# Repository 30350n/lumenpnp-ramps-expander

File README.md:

## LumenPnP Ramps Expander

**Warning: This design hasn't been ordered/tested yet. Use at your own risk.**

I created this board to use as an expander for the MKS Gen L v2.1 I use to as a motherboard for
my LumenPnP.

It offers:

- 2 additional stepper drivers
- RS485 driver for feeders
- analog REV03 style vacuum sensors (I2C ADC option)
- extra power input to power feeders from a different (12V) PSU

While this was originally designed for the MKS Gen L v2.1, it should generally be compatible
with all ATmega2560 based RAMPS boards and maybe even other 3d printer boards that have the
12864 display expansion connectors.

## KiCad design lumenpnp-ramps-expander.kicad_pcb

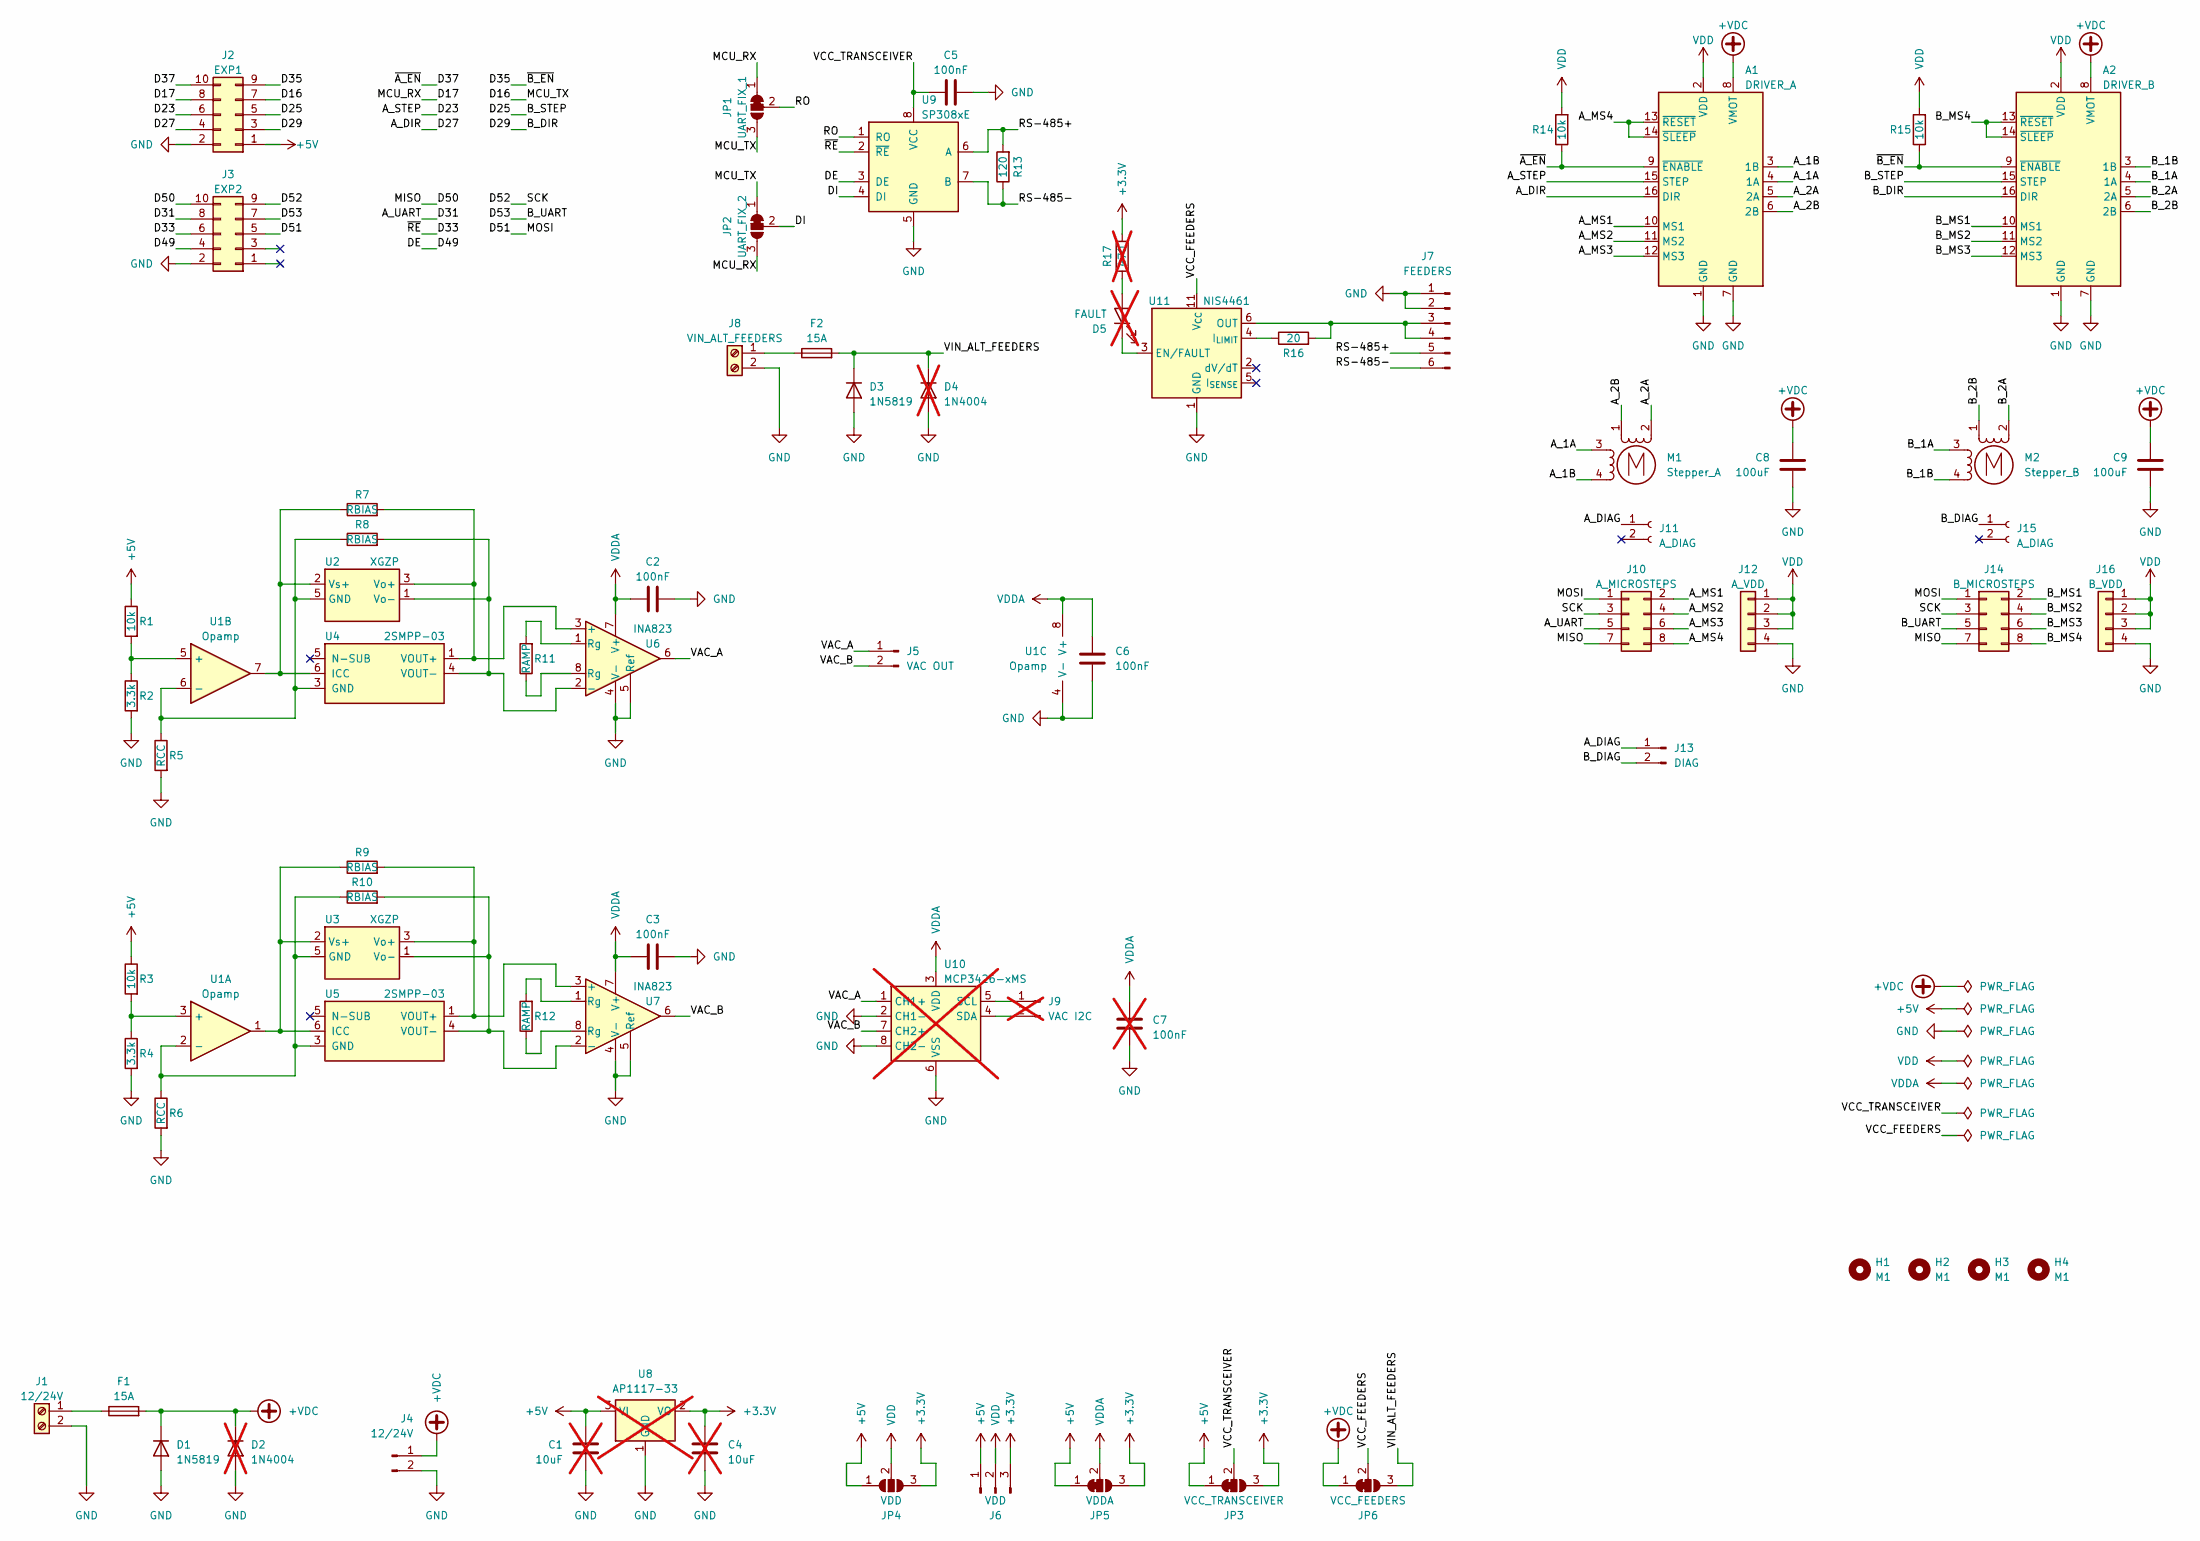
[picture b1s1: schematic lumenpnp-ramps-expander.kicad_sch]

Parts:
A1: DRIVER_A; Pololu_Breakout-16_15.2x20.3mm
A2: DRIVER_B; Pololu_Breakout-16_15.2x20.3mm
C1, C4: 10uF; C_1206_3216Metric; not fitted
C2, C3, C5, C6: 100nF; C_0603_1608Metric
C7: 100nF; C_0603_1608Metric; not fitted
C8, C9: 100uF; CP_Elec_6.3x7.7
D1, D3: 1N5819; D_SOD-123
D2, D4: 1N4004; D_DO-41_SOD81_P7.62mm_Horizontal; not fitted
D5: FAULT; LED_0603_1608Metric; not fitted
F1, F2: 15A; Fuse_1206_3216Metric
H1, H2, H3, H4: M1; MountingHole_3.2mm_M3_Pad
J1: 12/24V; TerminalBlock_Phoenix_MKDS-1,5-2-5.08_1x02_P5.08mm_Horizont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
J2: EXP1; IDC-Header_2x05_P2.54mm_Vertical
J3: EXP2; IDC-Header_2x05_P2.54mm_Vertical
J4: 12/24V; JST_XH_B2B-XH-A_1x02_P2.50mm_Vertical
J5: VAC OUT; JST_XH_B2B-XH-A_1x02_P2.50mm_Vertical
J6: VDD; PinHeader_1x03_P2.54mm_Vertical
J7: FEEDERS; IDC-Header_2x03_P2.54mm_Vertical
J8: VIN_ALT_FEEDERS; TerminalBlock_Phoenix_MKDS-1,5-2-5.08_1x02_P5.08mm_Horizont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
J9: VAC I2C; JST_XH_B2B-XH-A_1x02_P2.50mm_Vertical; not fitted
J10: A_MICROSTEPS; PinHeader_2x04_P2.54mm_Vertical
J11, J15: A_DIAG; PinSocket_1x02_P2.54mm_Vertical
J12: A_VDD; PinHeader_1x04_P2.54mm_Vertical
J13: DIAG; JST_XH_B2B-XH-A_1x02_P2.50mm_Vertical
J14: B_MICROSTEPS; PinHeader_2x04_P2.54mm_Vertical
J16: B_VDD; PinHeader_1x04_P2.54mm_Vertical
JP1: UART_FIX_1; SolderJumper-3_P1.3mm_Bridged12_RoundedPad1.0x1.5mm
JP2: UART_FIX_2; SolderJumper-3_P1.3mm_Bridged12_RoundedPad1.0x1.5mm
JP3: VCC_TRANSCEIVER; SolderJumper-3_P1.3mm_Bridged12_RoundedPad1.0x1.5mm
JP4: VDD; SolderJumper-3_P1.3mm_Open_RoundedPad1.0x1.5mm_NumberLabels
JP5: VDDA; SolderJumper-3_P1.3mm_Bridged12_RoundedPad1.0x1.5mm
JP6: VCC_FEEDERS; SolderJumper-3_P1.3mm_Bridged12_RoundedPad1.0x1.5mm
M1: Stepper_A; JST_XH_B4B-XH-A_1x04_P2.50mm_Vertical
M2: Stepper_B; JST_XH_B4B-XH-A_1x04_P2.50mm_Vertical
R1, R3, R14, R15: 10k; R_0603_1608Metric
R2, R4: 3.3k; R_0603_1608Metric
R5, R6: RCC; R_0603_1608Metric
R7, R8, R9, R10: RBIAS; R_0603_1608Metric
R11, R12: RAMP; R_0603_1608Metric
R13: 120; R_0603_1608Metric
R16: 20; R_0603_1608Metric
R17: 470; R_0603_1608Metric; not fitted
U1: Opamp; SOIC-8_3.9x4.9mm_P1.27mm
U2, U3: XGZP; SO-6_7x7mm_P2.54mm
U4, U5: 2SMPP-03
U6, U7: INA823; SOIC-8_3.9x4.9mm_P1.27mm
U8: AP1117-33; SOT-223-3_TabPin2; not fitted
U9: SP308xE; SOIC-8_3.9x4.9mm_P1.27mm
U10: MCP3426-xMS; SOIC-8_3.9x4.9mm_P1.27mm; not fitted
U11: NIS4461; WDFN-10-1EP_3x3mm_P0.5mm_EP1.8x2.5mm

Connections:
+3.3V: C4.1, J6.3, JP3.3 (B), JP4.3 (B), JP5.3 (B), R17.2, U8.2 (VO)
+5V: C1.1, J2.1, J6.1, JP3.1 (A), JP4.1 (A), JP5.1 (A), R1.1, R3.1, U8.3 (VI)
+VDC: A1.8 (VMOT), A2.8 (VMOT), C8.1, C9.1, D1.1 (K), D2.1 (K), F1.2, J4.1, JP6.1 (A)
/A_1A: A1.4 (1A), M1.3
/A_1B: A1.3 (1B), M1.4
/A_2A: A1.5 (2A), M1.2 (-)
/A_2B: A1.6 (2B), M1.1
/A_DIAG: J11.1, J13.1
/A_DIR: A1.16 (DIR), J2.4
/A_MS1: A1.10 (MS1), J10.2
/A_MS2: A1.11 (MS2), J10.4
/A_MS3: A1.12 (MS3), J10.6
/A_MS4: A1.13 (~RESET), A1.14 (~SLEEP), J10.8
/A_STEP: A1.15 (STEP), J2.6
/A_UART: J3.8, J10.5
/B_1A: A2.4 (1A), M2.3
/B_1B: A2.3 (1B), M2.4
/B_2A: A2.5 (2A), M2.2 (-)
/B_2B: A2.6 (2B), M2.1
/B_DIAG: J13.2, J15.1
/B_DIR: A2.16 (DIR), J2.3
/B_MS1: A2.10 (MS1), J14.2
/B_MS2: A2.11 (MS2), J14.4
/B_MS3: A2.12 (MS3), J14.6
/B_MS4: A2.13 (~RESET), A2.14 (~SLEEP), J14.8
/B_STEP: A2.15 (STEP), J2.5
/B_UART: J3.7, J14.5
/D16: J2.7, JP1.3 (B), JP2.1 (A)
/D17: J2.8, JP1.1 (A), JP2.3 (B)
/D33: J3.6, U9.2 (~RE)
/D35: A2.9 (~ENABLE), J2.9, R15.1
/D37: A1.9 (~ENABLE), J2.10, R14.1
/D49: J3.4, U9.3 (DE)
/D50: J3.10, J10.7, J14.7
/D51: J3.5, J10.1, J14.1
/D52: J3.9, J10.3, J14.3
/DI: JP2.2 (C), U9.4 (DI)
/RO: JP1.2 (C), U9.1 (RO)
/RS-485+: J7.5, R13.2, U9.6 (A)
/RS-485-: J7.6, R13.1, U9.7 (B)
/VAC_A: J5.1, U6.6, U10.1 (CH1+)
/VAC_B: J5.2, U7.6, U10.7 (CH2+)
/VCC_FEEDERS: JP6.2 (C), U11.11 (V_{CC})
/VCC_TRANSCEIVER: C5.1, JP3.2 (C), U9.8 (VCC)
/VIN_ALT_FEEDERS: D3.1 (K), D4.1 (K), F2.2, JP6.3 (B)
GND: A1.1 (GND), A1.7 (GND), A2.1 (GND), A2.7 (GND), C1.2, C2.2, C3.2, C4.2, C5.2, C6.2, C7.2, C8.2, C9.2, D1.2 (A), D2.2 (A), D3.2 (A), D4.2 (A), J1.2, J2.2, J3.2, J4.2, J7.1, J7.2, J8.2, J12.4, J16.4, R2.2, R4.2, R5.2, R6.2, U1.4 (V-), U6.4 (V-), U6.5 (Ref), U7.4 (V-), U7.5 (Ref), U8.1 (GND), U9.5 (GND), U10.2 (CH1-), U10.6 (VSS), U10.8 (CH2-), U11.1 (GND)
unnamed: D5.2 (A), R17.1
unnamed: D5.1 (K), U11.3 (EN/FAULT)
unnamed: F1.1, J1.1
unnamed: J7.3, J7.4, R16.2, U11.6 (OUT), U11.7 (OUT), U11.8 (OUT), U11.9 (OUT), U11.10 (OUT)
unnamed: F2.1, J8.1
unnamed: J9.1, U10.5 (SCL)
unnamed: J9.2, U10.4 (SDA)
unnamed: R11.1, U6.8 (Rg)
unnamed: R11.2, U6.1 (Rg)
unnamed: R12.1, U7.8 (Rg)
unnamed: R12.2, U7.1 (Rg)
unnamed: R3.2, R4.1, U1.3 (+)
unnamed: R6.1, R10.1, U1.2 (-), U3.5 (GND), U5.3 (GND)
unnamed: R1.2, R2.1, U1.5 (+)
unnamed: R5.1, R8.1, U1.6 (-), U2.5 (GND), U4.3 (GND)
unnamed: R7.2, U2.3 (Vo+), U4.1 (VOUT+), U6.3 (+)
unnamed: R7.1, U1.7, U2.2 (Vs+), U4.6 (ICC)
unnamed: R9.2, U3.3 (Vo+), U5.1 (VOUT+), U7.3 (+)
unnamed: R9.1, U1.1, U3.2 (Vs+), U5.6 (ICC)
unnamed: R8.2, U2.1 (Vo-), U2.6 (Vo-), U4.4 (VOUT-), U6.2 (-)
unnamed: R10.2, U3.1 (Vo-), U3.6 (Vo-), U5.4 (VOUT-), U7.2 (-)
unnamed: R16.1, U11.4 (I_{LIMIT})
VDD: A1.2 (VDD), A2.2 (VDD), J6.2, J12.1, J12.2, J12.3, J16.1, J16.2, J16.3, JP4.2 (C), R14.2, R15.2
VDDA: C2.1, C3.1, C6.1, C7.1, JP5.2 (C), U1.8 (V+), U6.7 (V+), U7.7 (V+), U10.3 (VDD)

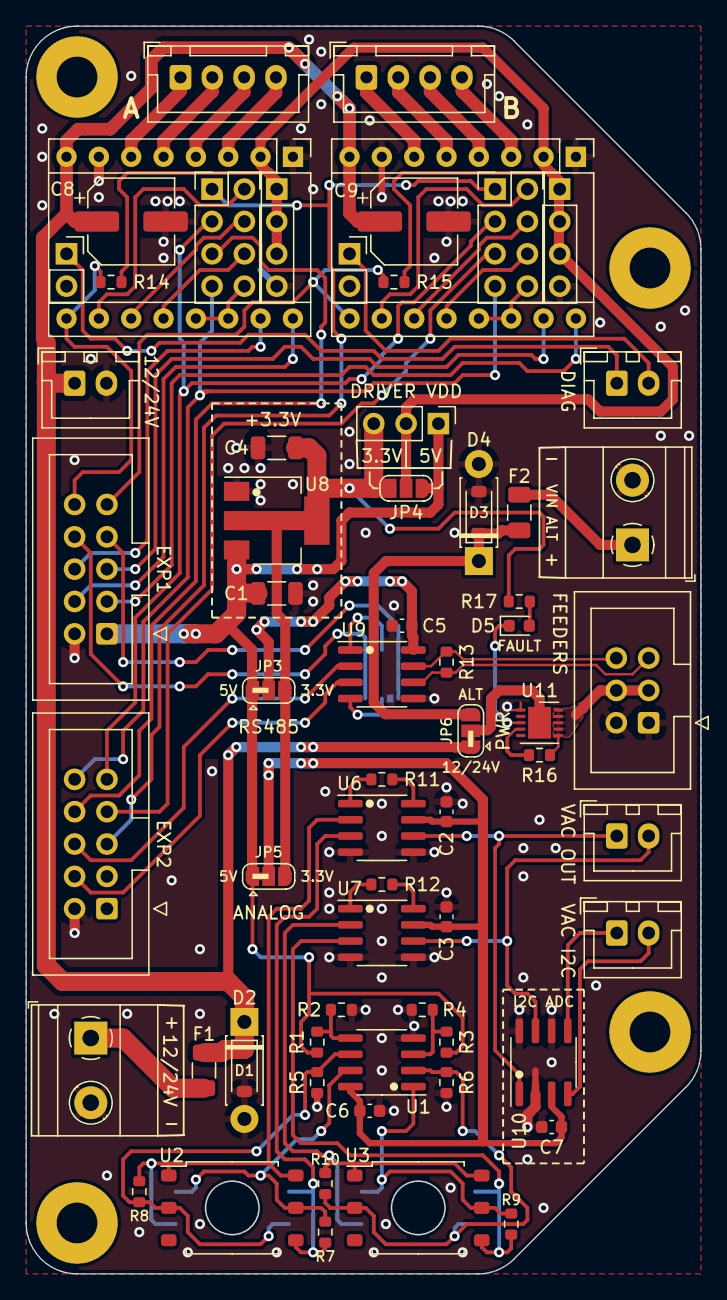
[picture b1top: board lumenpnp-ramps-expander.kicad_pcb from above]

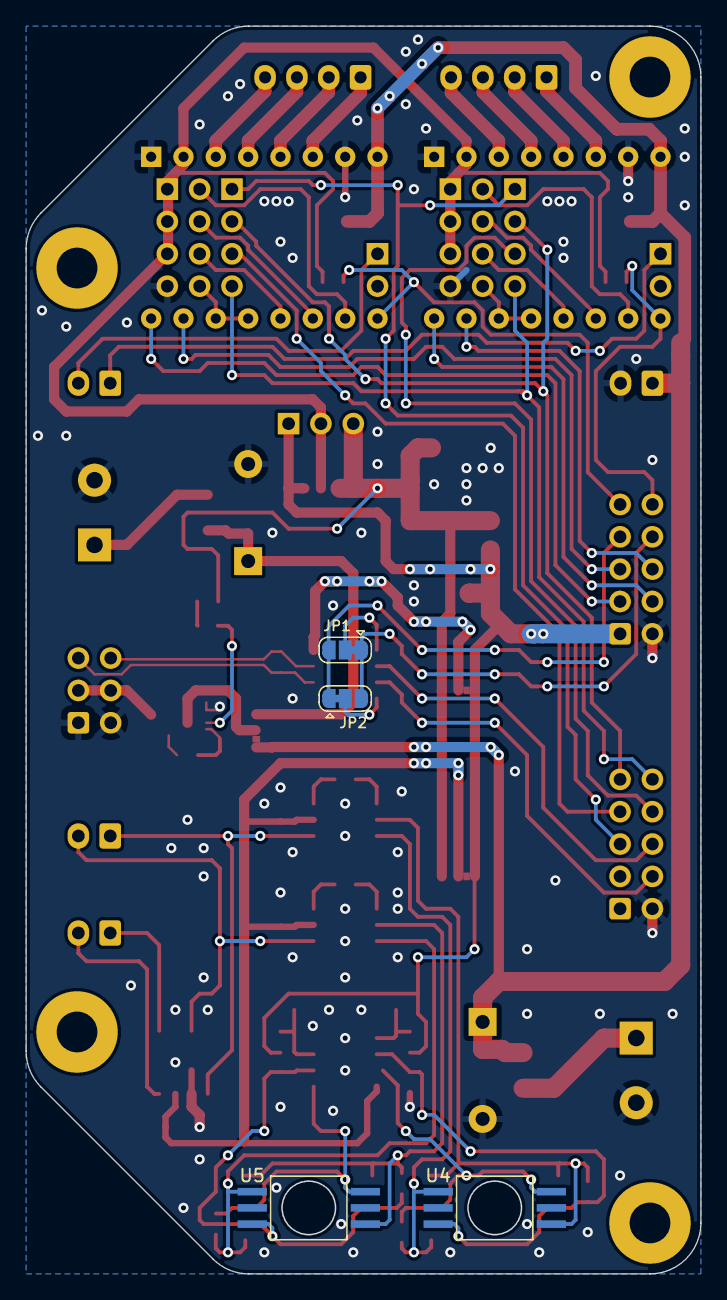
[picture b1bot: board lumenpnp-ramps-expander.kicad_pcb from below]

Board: 2 copper layers, 53.0 x 98.0 mm, 74 parts (2 on the bottom side), 70 nets.

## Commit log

2023-06-03 Add github preview image
2023-06-03 Add NIS4461 efuse for feeder power
